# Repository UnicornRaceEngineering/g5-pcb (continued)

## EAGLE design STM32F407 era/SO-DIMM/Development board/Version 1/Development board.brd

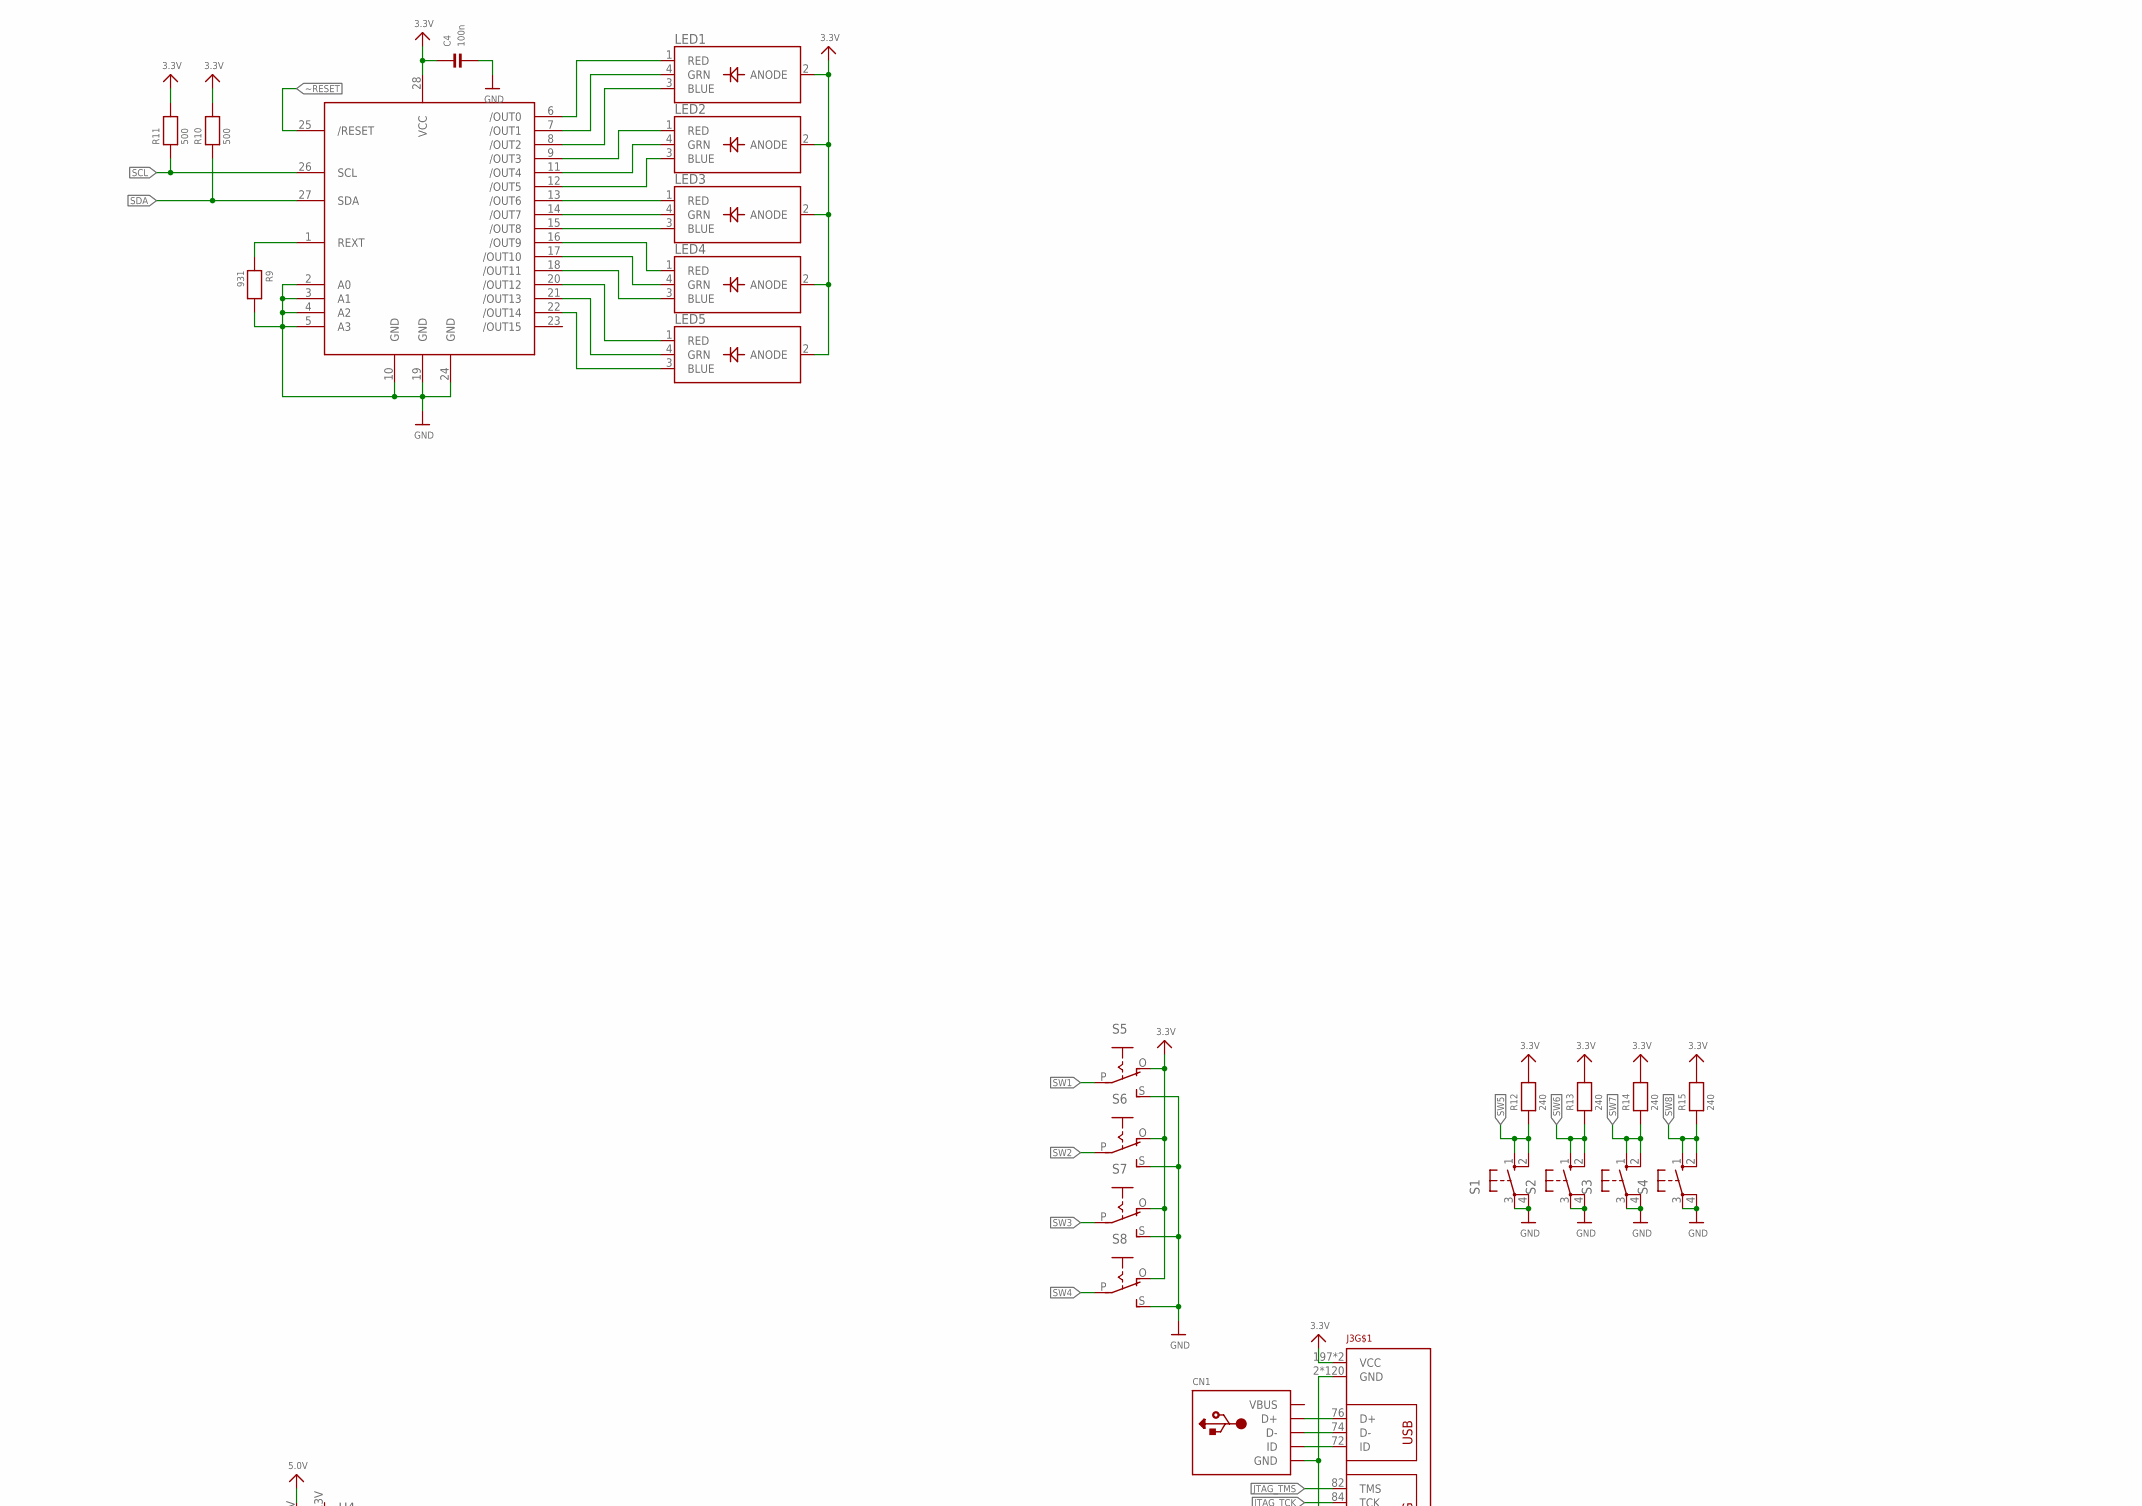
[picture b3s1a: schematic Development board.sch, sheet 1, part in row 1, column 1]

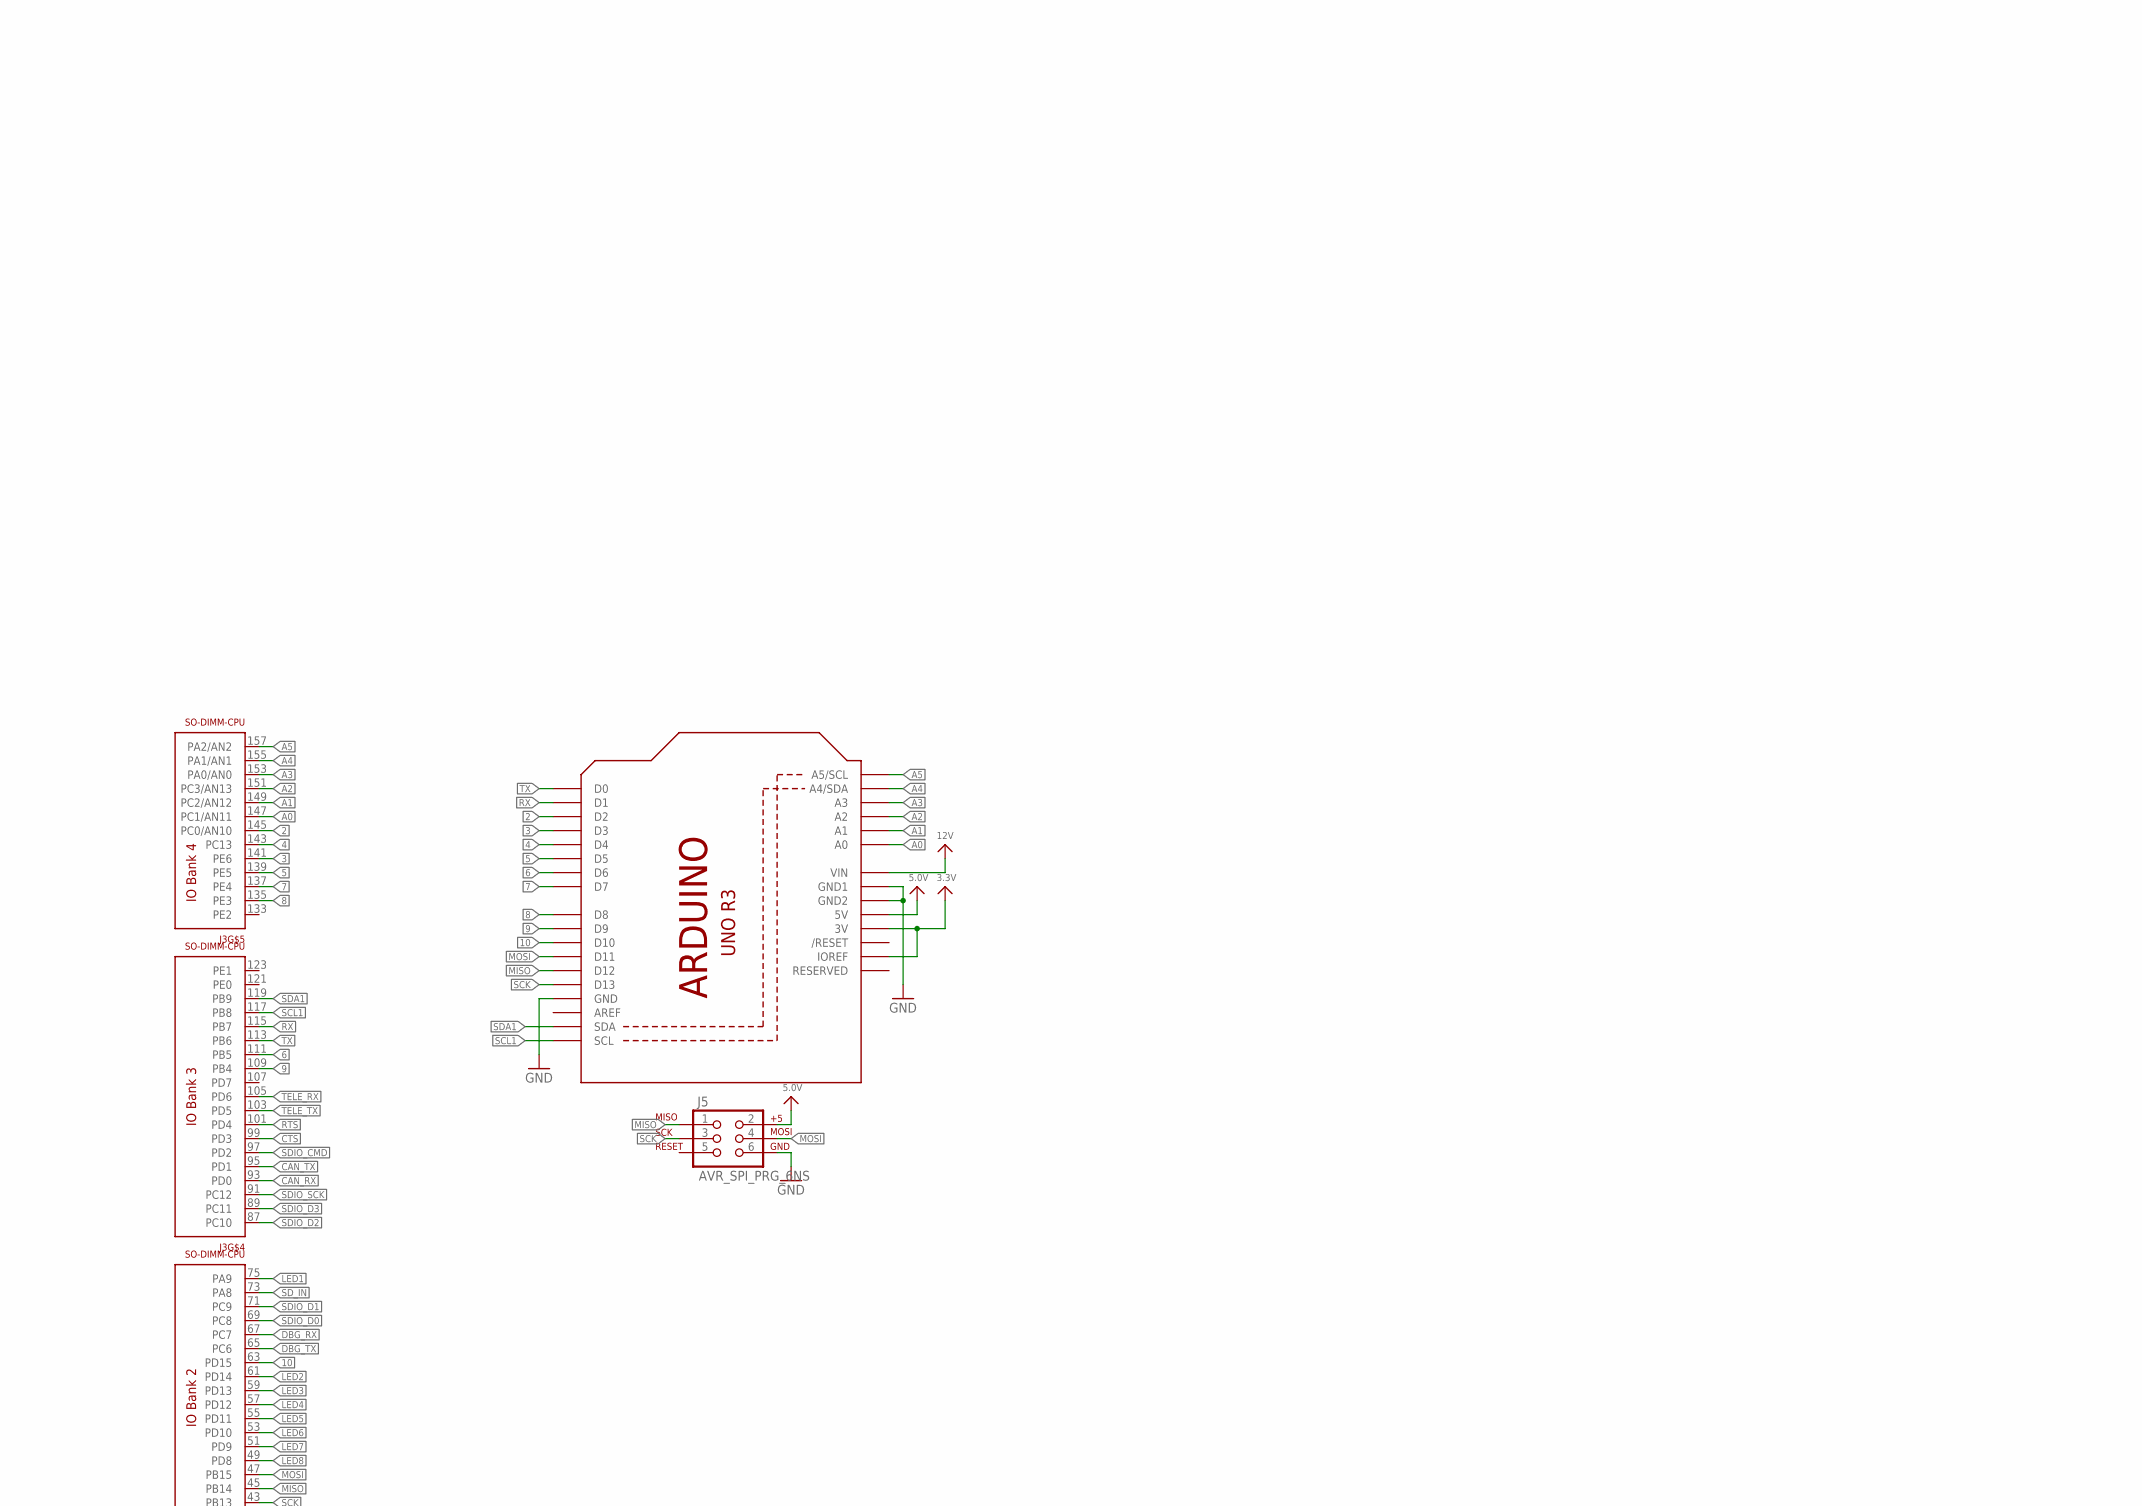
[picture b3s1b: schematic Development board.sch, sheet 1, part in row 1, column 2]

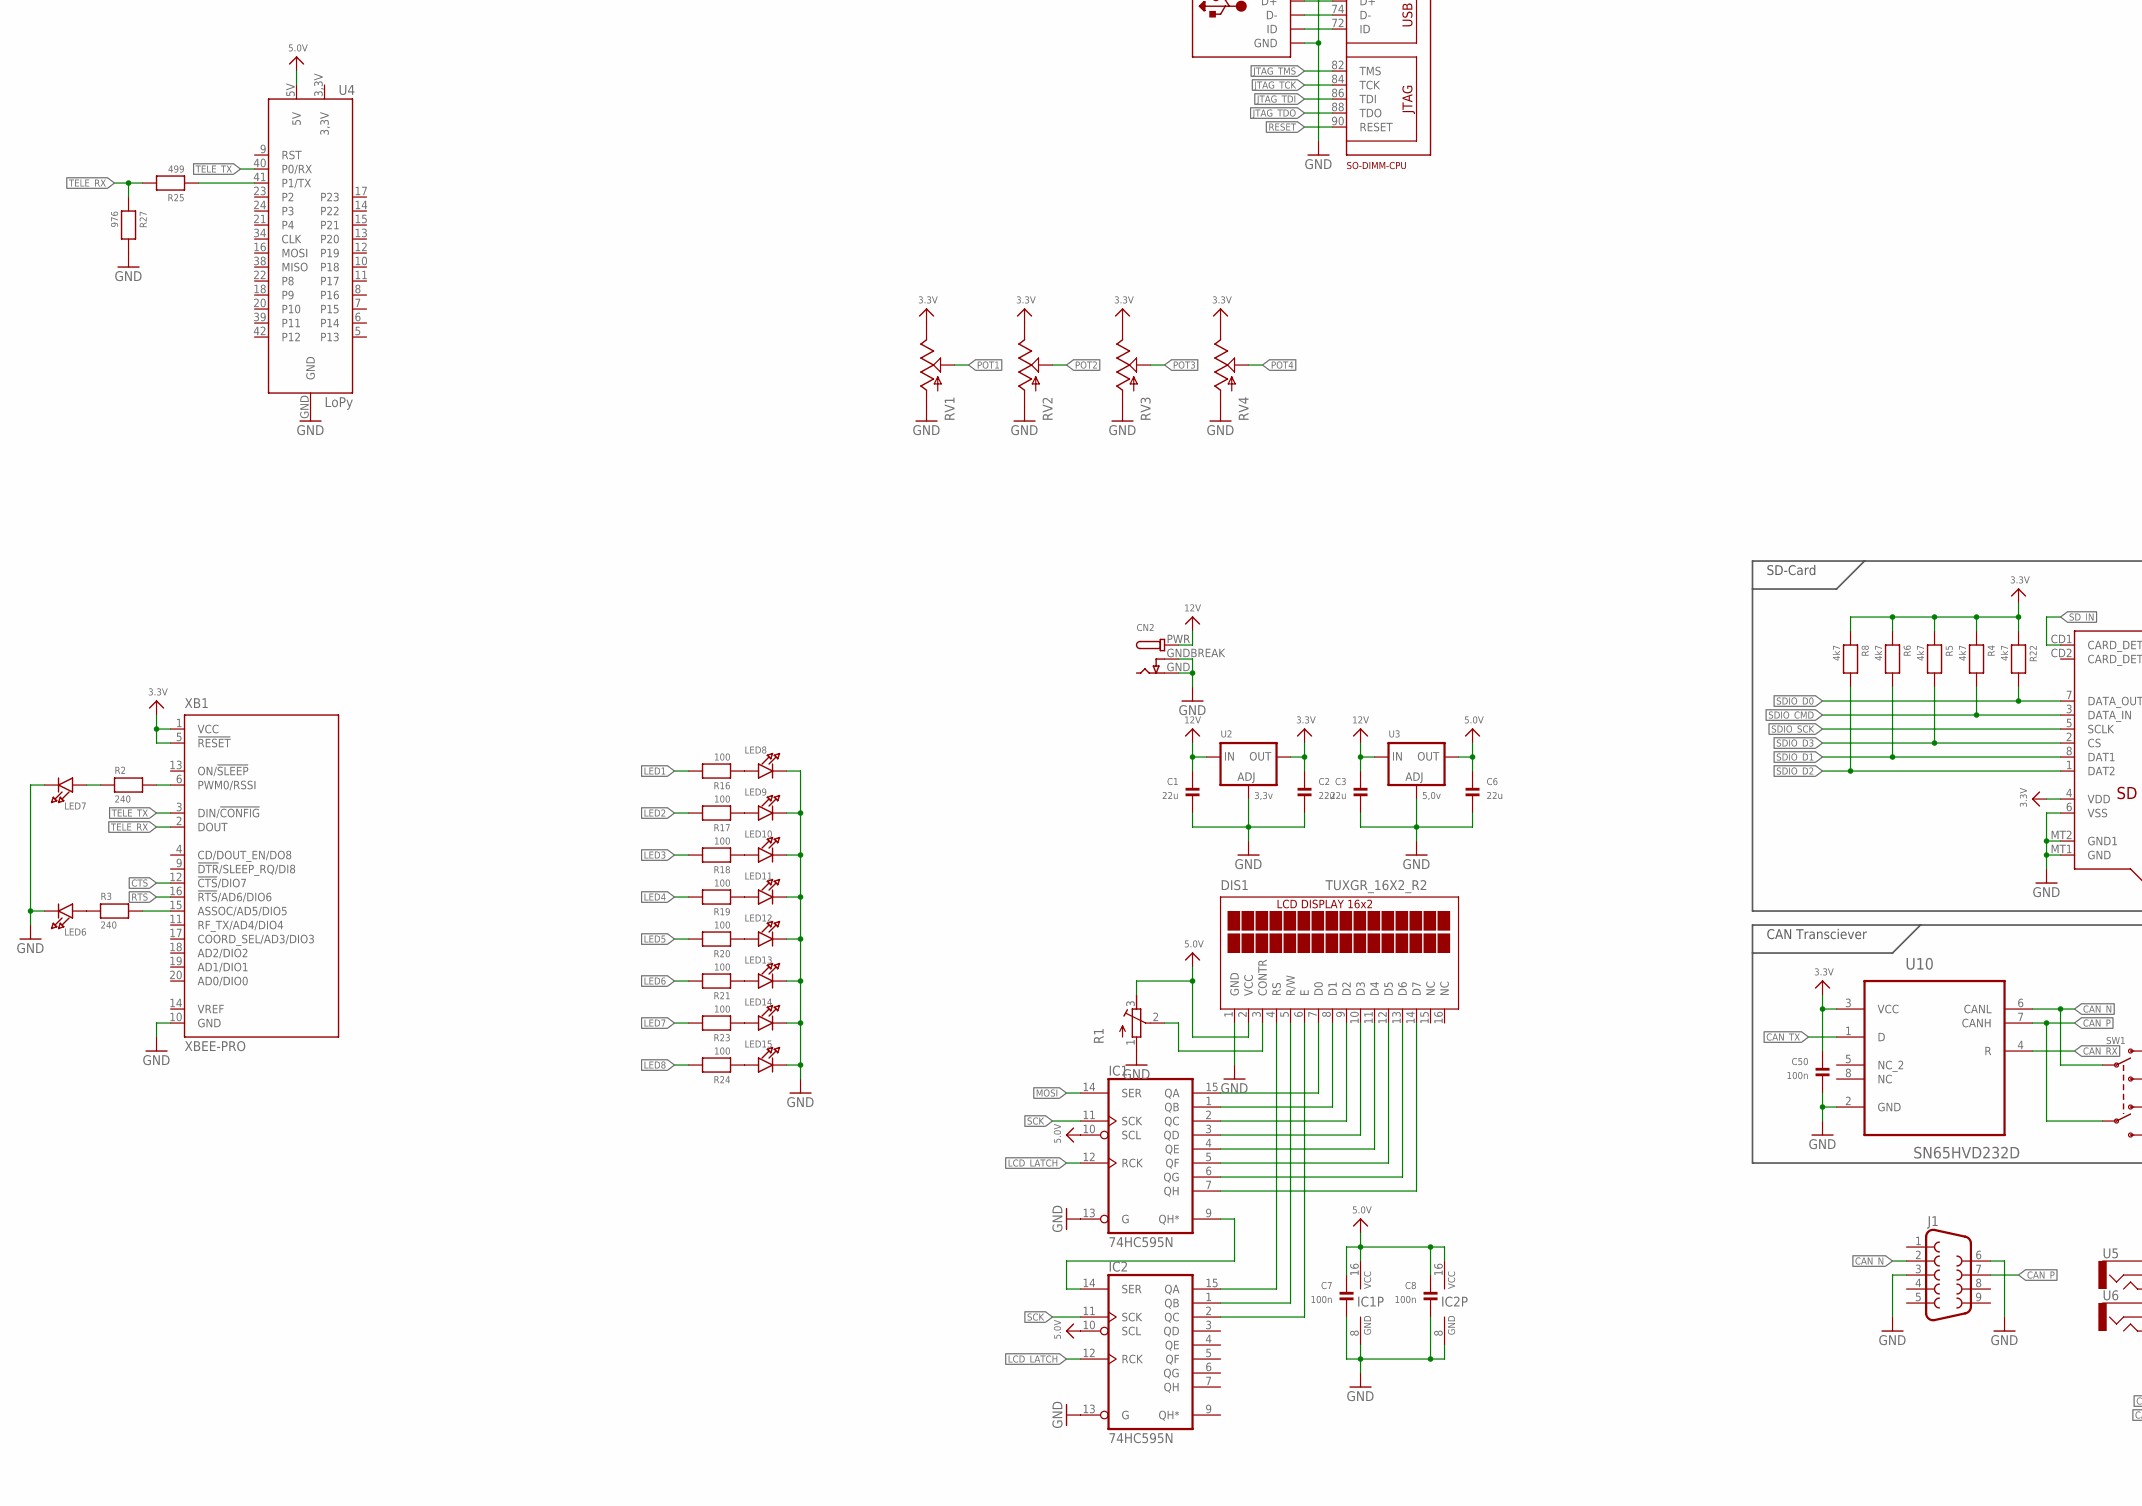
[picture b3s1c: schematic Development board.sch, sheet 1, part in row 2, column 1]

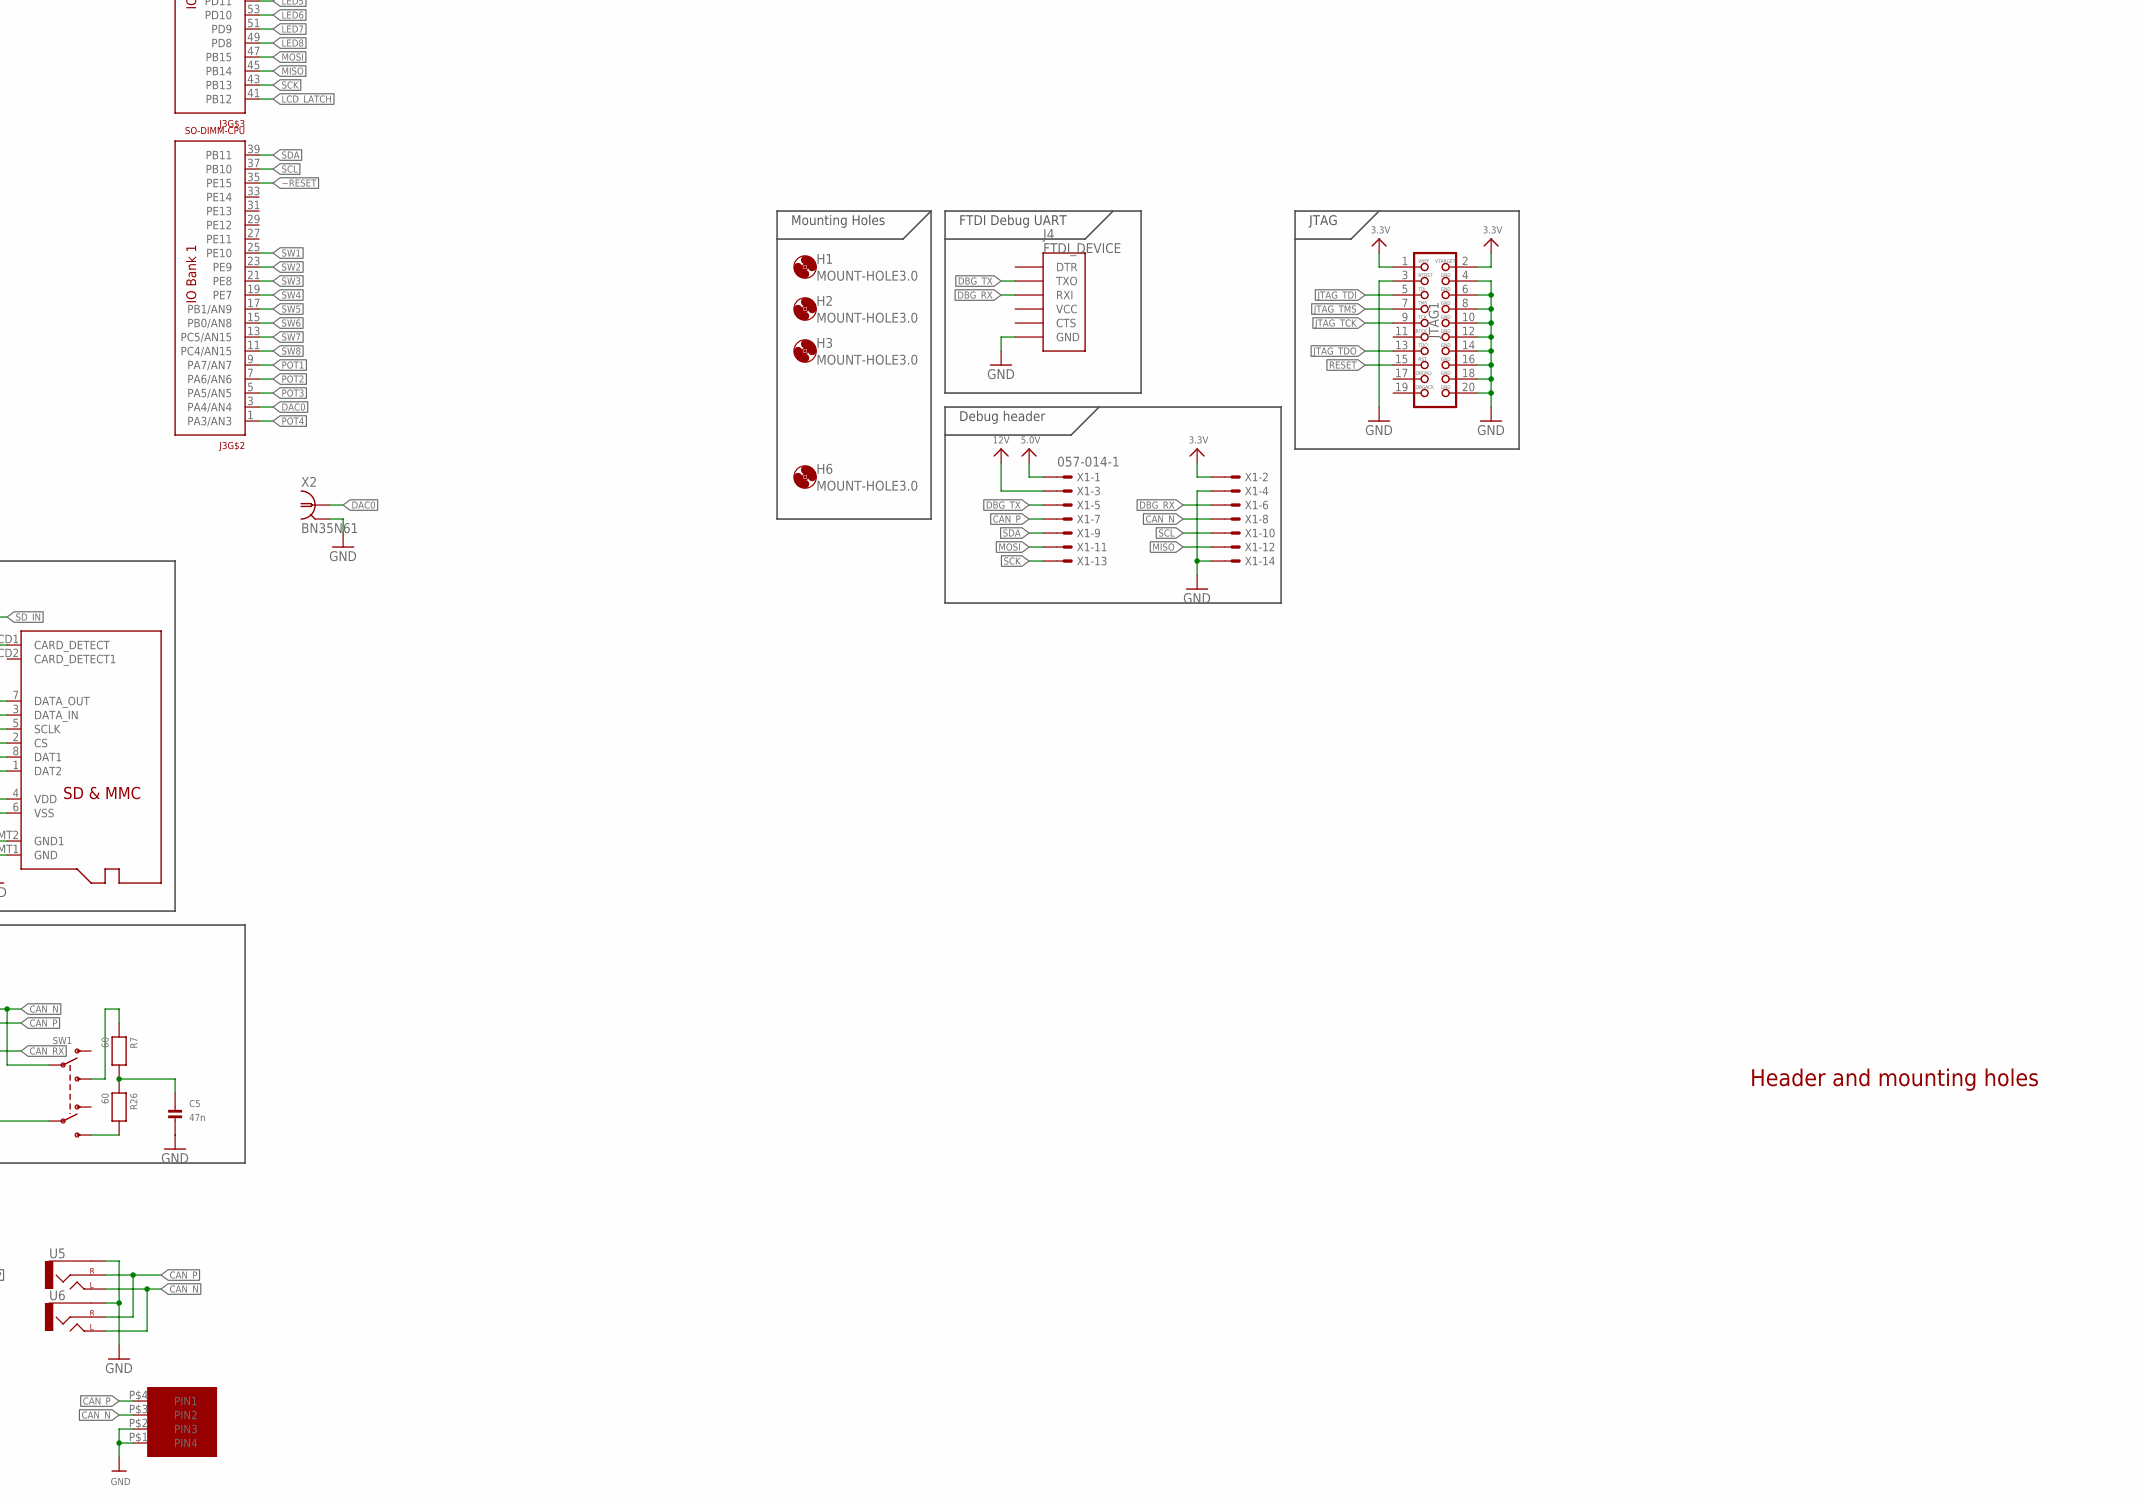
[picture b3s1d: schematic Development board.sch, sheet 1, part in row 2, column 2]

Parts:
C1, C2, C3, C6: 22u; _0805
C4, C7, C8, C50: 100n; _0603
C5: 47n; _0603
CN1: USBMINIBLARGE; USB-MINIB_LARGER
CN2: DCBARRELPTH; DCJACK_2MM_PTH
DIS1: TUXGR_16X2_R2
H1, H2, H3, H6: MOUNT-HOLE3.0; 3,0
IC1, IC2: 74HC595N; DIL16
J1: DB9FEMALE; DB9
J3: SO-DIMM-CPU; SODIMM-CONNECTOR-2.5V
J4: FTDI_DEVICE; FTDI_DEVICE_SIDE
J5: AVR_SPI_PRG_6NS; 2X3-NS
JTAG1: JTAG-ARM
LED1, LED2, LED3, LED4, LED5: LED_RGB_PLCC4; RGBLED_PLCC4
LED6, LED7, LED8, LED9, LED10, LED11, LED12, LED13, LED14, LED15: LED1206; CHIPLED_1206
R1: R-TRIMM3296W; RTRIM3296W
R2, R3, R12, R13, R14, R15: 240; _0603
R4, R5, R6, R8, R22: 4k7; _0603
R7, R26: 60; _0603
R9: 931; _0603
R10, R11: 500; _0603
R16, R17, R18, R19, R20, R21, R23, R24: 100; _0603
R25: 499; _0603
R27: 976; _0603
RV1, RV2, RV3, RV4: POT; ALPS_POT
S1, S2, S3, S4: 10-XX; B3F-10XX; MPN B3F-1000
S5, S6, S7, S8: EG1218S; EG1218
SW1: SWITCH_DPDT; DPDT_SMT_JS202011SCQN
U1: ARDUINOR3-DIMENSION; ARDUINOR3
U2: 3,3v; SOT223-R
U3: 5,0v; SOT223-R
U4: LoPy; LOPY
U5, U6: AUDIO-JACKPTH; AUDIO-JACK
U10: SN65HVD232D; SOIC127P600X175-8N
U$2: MICROSD
U$21: MICROFIT4; 43045-0400
U$30: TLC59116; TSSOP28
X1: 057-014-1
X2: BN35N61; B35N61
XB1: XBEE-PRO

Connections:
2: J3.145 (PC0/AN10), U1.D2
3: J3.141 (PE6), U1.D3
3.3V: C2.1, C4.1, C50.1, J3.197 (VCC), J3.199 (VCC), JTAG1.1, JTAG1.2, LED1.2 (ANODE), LED2.2 (ANODE), LED3.2 (ANODE), LED4.2 (ANODE), LED5.2 (ANODE), R4.1, R5.1, R6.1, R8.1, R10.2, R11.2, R12.2, R13.2, R14.2, R15.2, R22.1, RV1.P$1 (E), RV2.P$1 (E), RV3.P$1 (E), RV4.P$1 (E), S5.O, S6.O, S7.O, S8.O, U1.3V, U1.IOREF, U2.2 (OUT), U10.3 (VCC), U$2.4 (VDD), U$30.28 (VCC), X1.2, XB1.1 (VCC), XB1.5 (!RESET)
4: J3.143 (PC13), U1.D4
5: J3.139 (PE5), U1.D5
5.0V: C6.1, C7.1, C8.1, DIS1.2 (VCC), IC1.10 (SCL), IC1.16 (VCC), IC2.10 (SCL), IC2.16 (VCC), J5.2, R1.3 (E), U1.5V, U3.2 (OUT), U4.5V, X1.1
6: J3.111 (PB5), U1.D6
7: J3.137 (PE4), U1.D7
8: J3.135 (PE3), U1.D8
9: J3.109 (PB4), U1.D9
10: J3.63 (PD15), U1.D10
12V: C1.1, C3.1, CN2.PWR, U1.VIN, U2.3 (IN), U3.3 (IN), X1.3
A0: J3.147 (PC1/AN11), U1.A0
A1: J3.149 (PC2/AN12), U1.A1
A2: J3.151 (PC3/AN13), U1.A2
A3: J3.153 (PA0/AN0), U1.A3
A4: J3.155 (PA1/AN1), U1.A4 (A4/SDA)
A5: J3.157 (PA2/AN2), U1.A5 (A5/SCL)
CAN_N: J1.2, SW1.P$2 (P1), U5.TIP (LEFT), U6.TIP (LEFT), U10.6 (CANL), U$21.P$3 (PIN2), X1.8
CAN_P: J1.7, SW1.P$5 (P2), U5.RING (RIGHT), U6.RING (RIGHT), U10.7 (CANH), U$21.P$4 (PIN1), X1.7
CAN_RX: J3.93 (PD0), U10.4 (R)
CAN_TX: J3.95 (PD1), U10.1 (D)
CTS: J3.99 (PD3), XB1.12 (!CTS!/DIO7)
DAC0: J3.3 (PA4/AN4), X2.1
DBG_RX: J3.67 (PC7), J4.P$3 (RXI), X1.6
DBG_TX: J3.65 (PC6), J4.P$2 (TXO), X1.5
GND: C1.2, C2.2, C3.2, C4.2, C5.2, C6.2, C7.2, C8.2, C50.2, CN1.GND, CN2.GND, CN2.GNDBREAK, DIS1.1 (GND), IC1.8 (GND), IC1.13 (G), IC2.8 (GND), IC2.13 (G), J1.3, J1.6, J3.2 (GND), J3.4 (GND), J3.6 (GND), J3.8 (GND), J3.10 (GND), J3.12 (GND), J3.14 (GND), J3.16 (GND), J3.18 (GND), J3.20 (GND), J3.22 (GND), J3.24 (GND), J3.26 (GND), J3.28 (GND), J3.30 (GND), J3.32 (GND), J3.34 (GND), J3.36 (GND), J3.38 (GND), J3.40 (GND), J3.42 (GND), J3.44 (GND), J3.46 (GND), J3.48 (GND), J3.50 (GND), J3.52 (GND), J3.54 (GND), J3.56 (GND), J3.58 (GND), J3.60 (GND), J3.62 (GND), J3.64 (GND), J3.66 (GND), J3.68 (GND), J3.70 (GND), J3.77 (GND), J3.78 (GND), J3.79 (GND), J3.80 (GND), J3.81 (GND), J3.83 (GND), J3.85 (GND), J3.92 (GND), J3.94 (GND), J3.96 (GND), J3.98 (GND), J3.100 (GND), J3.102 (GND), J3.104 (GND), J3.106 (GND), J3.108 (GND), J3.110 (GND), J3.112 (GND), J3.114 (GND), J3.116 (GND), J3.118 (GND), J3.120 (GND), J3.122 (GND), J3.124 (GND), J3.125 (GND), J3.126 (GND), J3.127 (GND), J3.128 (GND), J3.129 (GND), J3.130 (GND), J3.131 (GND), J3.132 (GND), J3.134 (GND), J3.136 (GND), J3.138 (GND), J3.140 (GND), J3.142 (GND), J3.144 (GND), J3.146 (GND), J3.148 (GND), J3.150 (GND), J3.152 (GND), J3.154 (GND), J3.156 (GND), J3.158 (GND), J3.159 (GND), J3.160 (GND), J3.161 (GND), J3.162 (GND), J3.163 (GND), J3.164 (GND), J3.165 (GND), J3.166 (GND), J3.167 (GND), J3.168 (GND), J3.169 (GND), J3.170 (GND), J3.171 (GND), J3.172 (GND), J3.173 (GND), J3.174 (GND), J3.175 (GND), J3.176 (GND), J3.177 (GND), J3.178 (GND), J3.179 (GND), J3.180 (GND), J3.181 (GND), J3.182 (GND), J3.183 (GND), J3.184 (GND), J3.185 (GND), J3.186 (GND), J3.187 (GND), J3.188 (GND), J3.189 (GND), J3.190 (GND), J3.191 (GND), J3.192 (GND), J3.193 (GND), J3.194 (GND), J3.195 (GND), J3.196 (GND), J3.198 (GND), J3.200 (GND), J4.P$6 (GND), J5.6, JTAG1.3, JTAG1.4, JTAG1.6, JTAG1.8, JTAG1.10, JTAG1.12, JTAG1.14, JTAG1.16, JTAG1.18, JTAG1.20, LED6.C, LED7.C, LED8.C, LED9.C, LED10.C, LED11.C, LED12.C, LED13.C, LED14.C, LED15.C, R1.1 (A), R9.2, R27.2, RV1.P$3 (A), RV2.P$3 (A), RV3.P$3 (A), RV4.P$3 (A), S1.3, S1.4 (P1), S2.3, S2.4 (P1), S3.3, S3.4 (P1), S4.3, S4.4 (P1), S5.S, S6.S, S7.S, S8.S, U1.GND, U1.GND1, U1.GND2, U2.1 (ADJ), U3.1 (ADJ), U4.GND, U5.SLEEVE, U6.SLEEVE, U10.2 (GND), U$2.6 (VSS), U$2.MT1 (GND), U$2.MT2 (GND1), U$21.P$1 (PIN4), U$21.P$2 (PIN3), U$30.2 (A0), U$30.3 (A1), U$30.4 (A2), U$30.5 (A3), U$30.10 (GND), U$30.19 (GND), U$30.24 (GND), X1.4, X1.14, X2.2 (GND), X2.3 (GND), X2.4 (GND), X2.5 (GND), XB1.10 (GND)
JTAG_TCK: J3.84 (TCK), JTAG1.9
JTAG_TDI: J3.86 (TDI), JTAG1.5
JTAG_TDO: J3.88 (TDO), JTAG1.13
JTAG_TMS: J3.82 (TMS), JTAG1.7
LCD_LATCH: IC1.12 (RCK), IC2.12 (RCK), J3.41 (PB12)
LED1: J3.75 (PA9), R16.2
LED2: J3.61 (PD14), R17.2
LED3: J3.59 (PD13), R18.2
LED4: J3.57 (PD12), R19.2
LED5: J3.55 (PD11), R20.2
LED6: J3.53 (PD10), R21.2
LED7: J3.51 (PD9), R23.2
LED8: J3.49 (PD8), R24.2
MISO: J3.45 (PB14), J5.1, U1.D12, X1.12
MOSI: IC1.14 (SER), J3.47 (PB15), J5.4, U1.D11, X1.11
unnamed: DIS1.7 (D0), IC1.15 (QA)
unnamed: DIS1.8 (D1), IC1.1 (QB)
unnamed: R7.1, SW1.P$3 (S1)
unnamed: DIS1.9 (D2), IC1.2 (QC)
unnamed: R26.2, SW1.P$4 (S2)
unnamed: DIS1.10 (D3), IC1.3 (QD)
unnamed: DIS1.11 (D4), IC1.4 (QE)
unnamed: C5.1, R7.2, R26.1
unnamed: DIS1.12 (D5), IC1.5 (QF)
unnamed: LED1.1 (RED), U$30.6 (/OUT0)
unnamed: DIS1.3 (CONTR), R1.2 (S)
unnamed: LED8.A, R16.1
unnamed: LED1.4 (GRN), U$30.7 (/OUT1)
unnamed: LED1.3 (BLUE), U$30.8 (/OUT2)
unnamed: LED9.A, R17.1
unnamed: LED6.A, R3.1
unnamed: R3.2, XB1.15 (ASSOC/AD5/DIO5)
unnamed: R2.2, XB1.6 (PWM0/RSSI)
unnamed: LED7.A, R2.1
unnamed: LED2.1 (RED), U$30.9 (/OUT3)
unnamed: LED2.4 (GRN), U$30.11 (/OUT4)
unnamed: LED2.3 (BLUE), U$30.12 (/OUT5)
unnamed: DIS1.13 (D6), IC1.6 (QG)
unnamed: DIS1.14 (D7), IC1.7 (QH)
unnamed: LED10.A, R18.1
unnamed: LED11.A, R19.1
unnamed: IC1.9 (QH*), IC2.14 (SER)
unnamed: DIS1.4 (RS), IC2.15 (QA)
unnamed: LED3.1 (RED), U$30.13 (/OUT6)
unnamed: LED3.4 (GRN), U$30.14 (/OUT7)
unnamed: LED12.A, R20.1
unnamed: LED3.3 (BLUE), U$30.15 (/OUT8)
unnamed: LED4.1 (RED), U$30.16 (/OUT9)
unnamed: LED4.4 (GRN), U$30.17 (/OUT10)
unnamed: LED4.3 (BLUE), U$30.18 (/OUT11)
unnamed: LED5.1 (RED), U$30.20 (/OUT12)
unnamed: DIS1.5 (R/W), IC2.1 (QB)
unnamed: LED5.4 (GRN), U$30.21 (/OUT13)
unnamed: LED5.3 (BLUE), U$30.22 (/OUT14)
unnamed: DIS1.6 (E), IC2.2 (QC)
unnamed: LED13.A, R21.1
unnamed: LED14.A, R23.1
unnamed: LED15.A, R24.1
unnamed: R25.1, U4.41 (P1/TX)
unnamed: R9.1, U$30.1 (REXT)
unnamed: CN1.ID, J3.72 (ID)
POT1: J3.9 (PA7/AN7), RV1.P$2 (S)
POT2: J3.7 (PA6/AN6), RV2.P$2 (S)
POT3: J3.5 (PA5/AN5), RV3.P$2 (S)
POT4: J3.1 (PA3/AN3), RV4.P$2 (S)
RESET: J3.90 (RESET), JTAG1.15
RTS: J3.101 (PD4), XB1.16 (!RTS!/AD6/DIO6)
RX: J3.115 (PB7), U1.D1
SCK: IC1.11 (SCK), IC2.11 (SCK), J3.43 (PB13), J5.3, U1.D13, X1.13
SCL: J3.37 (PB10), R11.1, U$30.26 (SCL), X1.10
SCL1: J3.117 (PB8), U1.SCL
SDA: J3.39 (PB11), R10.1, U$30.27 (SDA), X1.9
SDA1: J3.119 (PB9), U1.SDA
SDIO_CMD: J3.97 (PD2), R4.2, U$2.3 (DATA_IN)
SDIO_D0: J3.69 (PC8), R22.2, U$2.7 (DATA_OUT)
SDIO_D1: J3.71 (PC9), R6.2, U$2.8 (DAT1)
SDIO_D2: J3.87 (PC10), R8.2, U$2.1 (DAT2)
SDIO_D3: J3.89 (PC11), R5.2, U$2.2 (CS)
SDIO_SCK: J3.91 (PC12), U$2.5 (SCLK)
SD_IN: J3.73 (PA8), U$2.CD1 (CARD_DETECT)
SW1: J3.25 (PE10), S5.P
SW2: J3.23 (PE9), S6.P
SW3: J3.21 (PE8), S7.P
SW4: J3.19 (PE7), S8.P
SW5: J3.17 (PB1/AN9), R12.1, S1.1 (S), S1.2 (S1)
SW6: J3.15 (PB0/AN8), R13.1, S2.1 (S), S2.2 (S1)
SW7: J3.13 (PC5/AN15), R14.1, S3.1 (S), S3.2 (S1)
SW8: J3.11 (PC4/AN15), R15.1, S4.1 (S), S4.2 (S1)
TELE_RX: J3.105 (PD6), R25.2, R27.1, XB1.2 (DOUT)
TELE_TX: J3.103 (PD5), U4.40 (P0/RX), XB1.3 (DIN/!CONFIG)
TX: J3.113 (PB6), U1.D0
VBUS: CN1.VBUS
_N: CN1.D-, J3.74 (D-)
_P: CN1.D+, J3.76 (D+)
~RESET: J3.35 (PE15), U$30.25 (/RESET)

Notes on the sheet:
CAN Transciever
Mounting Holes
SD-Card
Header and mounting holes
JTAG
FTDI Debug UART
Debug header

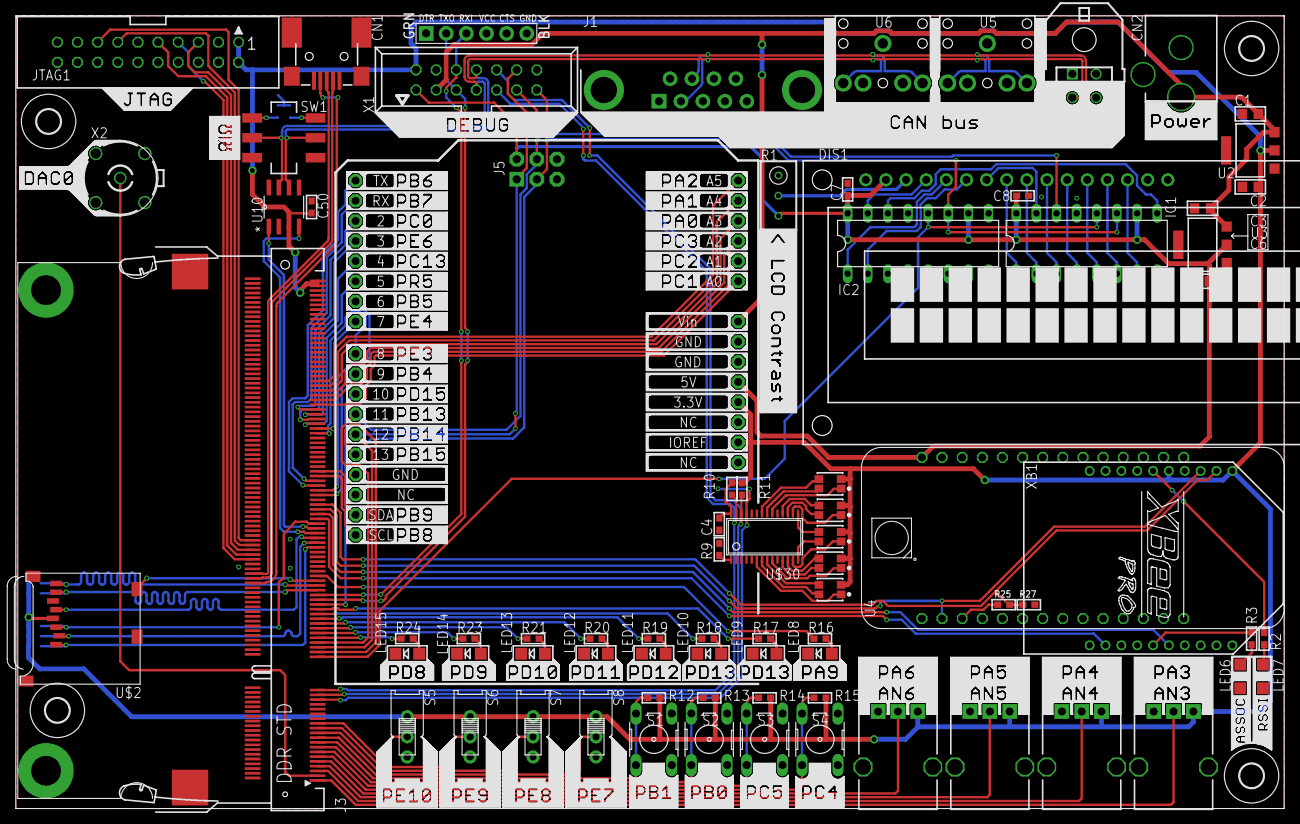
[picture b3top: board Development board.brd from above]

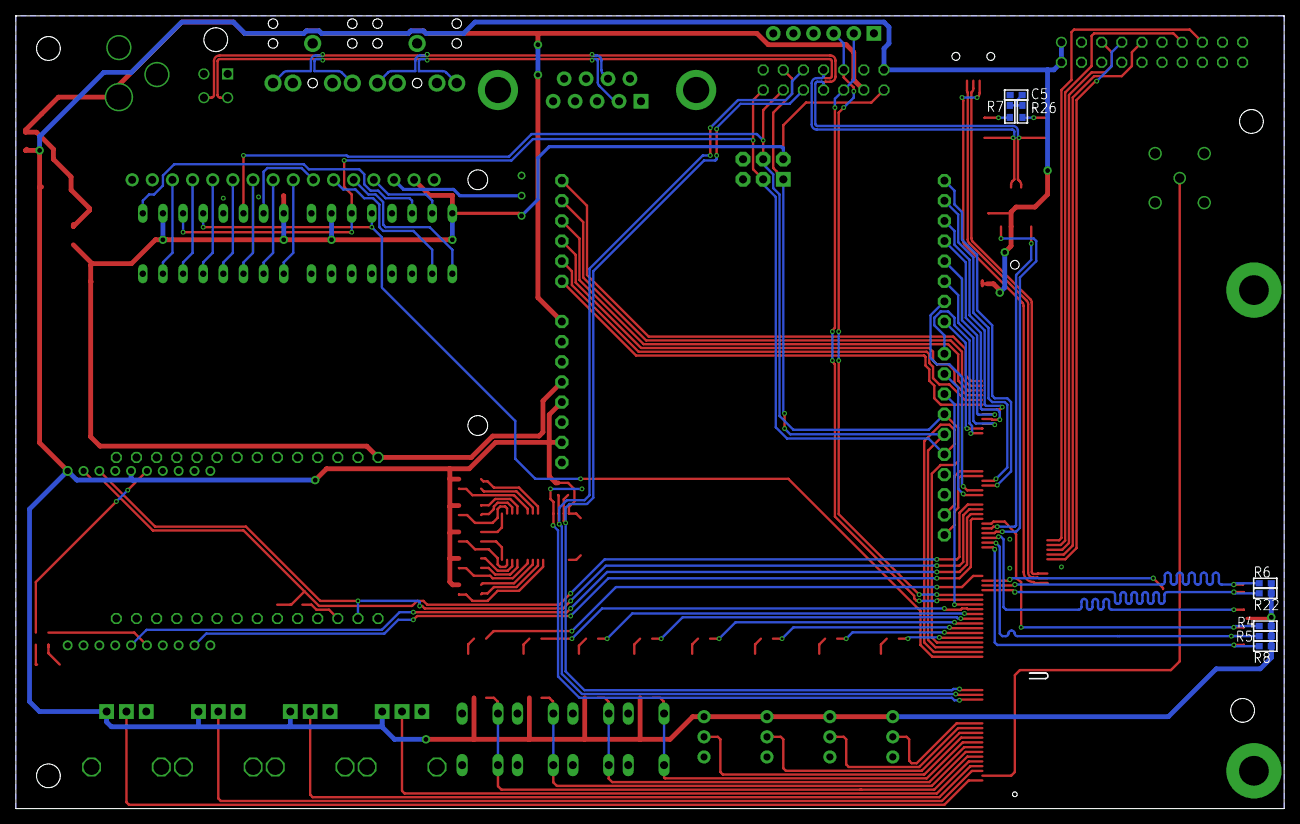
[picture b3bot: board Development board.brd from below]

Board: 2 copper layers, 160.0 x 100.0 mm, 91 parts (8 on the bottom side), 121 nets.
